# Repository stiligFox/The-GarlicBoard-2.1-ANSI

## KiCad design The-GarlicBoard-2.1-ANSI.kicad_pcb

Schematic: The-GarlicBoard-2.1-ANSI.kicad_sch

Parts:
C1, C2, C4, C6, C7, C8, C9, C10, C11, C15: 100nF; C_0402_1005Metric; Manufacturer Part No CL05B104KO5NNNC; LCSC C1525
C3, C5: 1uF; C_0402_1005Metric; Manufacturer Part No CL05A105KA5NQNC; LCSC C52923
C12, C13: 27pF; C_0402_1005Metric; Manufacturer Part No 0402CG270J500NT; LCSC C1557
C14, C16: 10uF; C_0805_2012Metric; Manufacturer Part No CL05A106MQ5NUNC; LCSC C1713
C17: 22uF; CP_EIA-3216-10_Kemet-I; LCSC C7171
C18, C21: 1uF; C_0603_1608Metric; LCSC C1592
C19, C20, C22: 100nF; C_0402_1005Metric; LCSC C1525
D1, D2, D3, D4, D5, D6, D7, D8, D9, D10, D11, D12, D13, D14, D15, D16, D17, D18, D19, D20, D21, D22, D23, D24, D25, D26, D27, D28, D29, D30, D31, D32, D33, D34, D35, D36, D37, D38, D39, D40, D41, D42, D43, D44, D45, D46, D47, D48, D49, D50, D51, D52, D53, D54, D55, D56, D57, D58, D59, D60, D61, D62, D63, D64, D65: D; D_SOD-523; Manufacturer Part No 1N5819WS; LCSC C282366
H1, H2, H3, H4, H5, H6, H7: MH; MountingHole_2.2mm_M2
J1, J3, J4, J5, J6: PAD_SQUARE_1MM
J2, J7: Molex Pico-EZMATE; Molex_Pico-EZmate_78171-0004_1x04-1MP_P1.20mm_Vertical; Manufacturer Part No 78170004; LCSC C588524
LED1: Debug LED; LED_0603_1608Metric; Manufacturer Part No C2290; LCSC C2290
Q1: Q_PMOS_GSD; SOT-323_SC-70; Manufacturer Part No DMP2165UW-7; LCSC C388477
R1, R2: 27.4; R_0402_1005Metric; Manufacturer Part No 0402WGF274JTCE; LCSC C31439
R3, R25, R26: 1k; R_0402_1005Metric; Manufacturer Part No 0402WGF1001TCE; LCSC C11702
R6: 120; R_0402_1005Metric; Manufacturer Part No 0402WGF1200TCE; LCSC C25079
R7, R10, R13, R16, R19, R22: 33; R_0603_1608Metric; LCSC C23140
R8, R9, R11, R12, R14, R15, R17, R18, R20, R21, R23, R24: 28; R_0603_1608Metric; LCSC C22973
R27: DNF; R_0402_1005Metric
R28: 10k; R_0402_1005Metric; LCSC C25531
RGB1, RGB2, RGB3, RGB4, RGB5, RGB6, RGB7, RGB8, RGB9, RGB10, RGB11, RGB12, RGB13, RGB14, RGB15, RGB16, RGB17, RGB18, RGB19, RGB20, RGB21, RGB22, RGB23, RGB24, RGB25, RGB26, RGB27, RGB28, RGB29, RGB30, RGB31, RGB32, RGB33, RGB34, RGB35, RGB36, RGB37, RGB38, RGB39, RGB40, RGB41, RGB42, RGB43, RGB44, RGB45, RGB46, RGB47, RGB48, RGB49, RGB50, RGB51, RGB52, RGB53, RGB54, RGB55, RGB56, RGB57, RGB58, RGB59, RGB60, RGB61, RGB62, RGB63, RGB64: LED_RGBA; LED_MX_6028R FIXED; LCSC C183826
ST1, ST5: Stabilizer; STAB_MX_3u
ST2, ST3: Stabilizer; STAB_MX_2.25u
ST4: Stabilizer; STAB_MX_2.75u
SW1: ESC; SW_MX_HS_1.5u; Manufacturer Part No CPG151101S11-1; LCSC C5156480
SW2: TAB; SW_MX_HS_1.75u; Manufacturer Part No CPG151101S11-1; LCSC C5156480
SW3: L_SHIFT; SW_MX_HS_1u; Manufacturer Part No CPG151101S11-1; LCSC C5156480
SW4: L_CTRL; SW_MX_HS_1.25u; Manufacturer Part No CPG151101S11-1; LCSC C5156480
SW5: Q; SW_MX_HS_1u; Manufacturer Part No CPG151101S11-1; LCSC C5156480
SW6: A; SW_MX_HS_1u; Manufacturer Part No CPG151101S11-1; LCSC C5156480
SW7: Z; SW_MX_HS_1u; Manufacturer Part No CPG151101S11-1; LCSC C5156480
SW8: L_ALT; SW_MX_HS_1.25u; Manufacturer Part No CPG151101S11-1; LCSC C5156480
SW9: W; SW_MX_HS_1u; Manufacturer Part No CPG151101S11-1; LCSC C5156480
SW10: S; SW_MX_HS_1u; Manufacturer Part No CPG151101S11-1; LCSC C5156480
SW11: X; SW_MX_HS_1u; Manufacturer Part No CPG151101S11-1; LCSC C5156480
SW12: L_CMD; SW_MX_HS_1.25u; Manufacturer Part No CPG151101S11-1; LCSC C5156480
SW13: E; SW_MX_HS_1u; Manufacturer Part No CPG151101S11-1; LCSC C5156480
SW14: D; SW_MX_HS_1u; Manufacturer Part No CPG151101S11-1; LCSC C5156480
SW15: C; SW_MX_HS_1u; Manufacturer Part No CPG151101S11-1; LCSC C5156480
SW16: R; SW_MX_HS_1u; Manufacturer Part No CPG151101S11-1; LCSC C5156480
SW17: F; SW_MX_HS_1u; Manufacturer Part No CPG151101S11-1; LCSC C5156480
SW18: V; SW_MX_HS_1u; Manufacturer Part No CPG151101S11-1; LCSC C5156480
SW19: FN_1; SW_MX_HS_1u; Manufacturer Part No CPG151101S11-1; LCSC C5156480
SW20: T; SW_MX_HS_1u; Manufacturer Part No CPG151101S11-1; LCSC C5156480
SW21: G; SW_MX_HS_1u; Manufacturer Part No CPG151101S11-1; LCSC C5156480
SW22: B; SW_MX_HS_1u; Manufacturer Part No CPG151101S11-1; LCSC C5156480
SW23: Y; SW_MX_HS_1u; Manufacturer Part No CPG151101S11-1; LCSC C5156480
SW24: H; SW_MX_HS_1u; Manufacturer Part No CPG151101S11-1; LCSC C5156480
SW25: N; SW_MX_HS_1u; Manufacturer Part No CPG151101S11-1; LCSC C5156480
SW26: SPACE; SW_MX_HS_1u; Manufacturer Part No CPG151101S11-1; LCSC C5156480
SW27: U; SW_MX_HS_1u; Manufacturer Part No CPG151101S11-1; LCSC C5156480
SW28: J; SW_MX_HS_1u; Manufacturer Part No CPG151101S11-1; LCSC C5156480
SW29: M; SW_MX_HS_1u; Manufacturer Part No CPG151101S11-1; LCSC C5156480
SW30: I; SW_MX_HS_1u; Manufacturer Part No CPG151101S11-1; LCSC C5156480
SW31: K; SW_MX_HS_1u; Manufacturer Part No CPG151101S11-1; LCSC C5156480
SW32: COMMA; SW_MX_HS_1u; Manufacturer Part No CPG151101S11-1; LCSC C5156480
SW33: R_CMD; SW_MX_HS_1.25u; Manufacturer Part No CPG151101S11-1; LCSC C5156480
SW34: O; SW_MX_HS_1u; Manufacturer Part No CPG151101S11-1; LCSC C5156480
SW35: L; SW_MX_HS_1u; Manufacturer Part No CPG151101S11-1; LCSC C5156480
SW36: PERIOD; SW_MX_HS_1u; Manufacturer Part No CPG151101S11-1; LCSC C5156480
SW37: P; SW_MX_HS_1u; Manufacturer Part No CPG151101S11-1; LCSC C5156480
SW38: SEMI_COLON; SW_MX_HS_1u; Manufacturer Part No CPG151101S11-1; LCSC C5156480
SW39: SLASH; SW_MX_HS_1u; Manufacturer Part No CPG151101S11-1; LCSC C5156480
SW40: R_ALT; SW_MX_HS_1.25u; Manufacturer Part No CPG151101S11-1; LCSC C5156480
SW41: HYPHEN; SW_MX_HS_1u; Manufacturer Part No CPG151101S11-1; LCSC C5156480
SW42: APOSTROPHE; SW_MX_HS_1u; Manufacturer Part No CPG151101S11-1; LCSC C5156480
SW43: R_CTRL; SW_MX_HS_1.25u; Manufacturer Part No CPG151101S11-1; LCSC C5156480
SW44: EQUALS; SW_MX_HS_1u; Manufacturer Part No CPG151101S11-1; LCSC C5156480
SW45: RETURN; SW_MX_HS_1u; Manufacturer Part No CPG151101S11-1; LCSC C5156480
SW46: FN_2; SW_MX_HS_1.5u; Manufacturer Part No CPG151101S11-1; LCSC C5156480
SW47: BCK_SPC; SW_MX_HS_1.5u; Manufacturer Part No CPG151101S11-1; LCSC C5156480
SW48: R_SHIFT; SW_MX_HS_1u; Manufacturer Part No CPG151101S11-1; LCSC C5156480
SW49: 7; SW_MX_HS_1u; Manufacturer Part No CPG151101S11-1; LCSC C5156480
SW50: 4; SW_MX_HS_1u; Manufacturer Part No CPG151101S11-1; LCSC C5156480
SW51: 1; SW_MX_HS_1u; Manufacturer Part No CPG151101S11-1; LCSC C5156480
SW52: 00; SW_MX_HS_1u; Manufacturer Part No CPG151101S11-1; LCSC C5156480
SW53: 8; SW_MX_HS_1u; Manufacturer Part No CPG151101S11-1; LCSC C5156480
SW54: 5; SW_MX_HS_1u; Manufacturer Part No CPG151101S11-1; LCSC C5156480
SW55: 2; SW_MX_HS_1u; Manufacturer Part No CPG151101S11-1; LCSC C5156480
SW56: 0; SW_MX_HS_1u; Manufacturer Part No CPG151101S11-1; LCSC C5156480
SW57: 9; SW_MX_HS_1u; Manufacturer Part No CPG151101S11-1; LCSC C5156480
SW58: 6; SW_MX_HS_1u; Manufacturer Part No CPG151101S11-1; LCSC C5156480
SW59: 3; SW_MX_HS_1u; Manufacturer Part No CPG151101S11-1; LCSC C5156480
SW60: NUM_PER; SW_MX_HS_1u; Manufacturer Part No CPG151101S11-1; LCSC C5156480
SW61: MINUS; SW_MX_HS_1u; Manufacturer Part No CPG151101S11-1; LCSC C5156480
SW62: PLUS; SW_MX_HS_1u; Manufacturer Part No CPG151101S11-1; LCSC C5156480
SW63: ENTER; SW_MX_HS_1u; Manufacturer Part No CPG151101S11-1; LCSC C5156480
SW64: PAD_LOCK; SW_MX_HS_1u; Manufacturer Part No CPG151101S11-1; LCSC C5156480
SW65: SW_Push; SW_SPST_SKQG_WithStem; Manufacturer Part No B3U-1000P; LCSC C115351
SW66, SW67: SW_Push; SW_SPST_B3U-1000P; Manufacturer Part No B3U-1000P; LCSC C231329
SW68: RotaryEncoder_Switch; RotaryEncoder_Alps_EC11E-Switch_Vertical_H20mm
U1: RP2040; QFN-56-1EP_7x7mm_P0.4mm_EP3.2x3.2mm; Manufacturer Part No RP2040; LCSC C2040
U2: W25Q128JVS; SOIC-8_5.23x5.23mm_P1.27mm; Manufacturer Part No W25Q128JVSIQ; LCSC C97521
U3: NCP1117-3.3_SOT223; SOT-223-3_TabPin2; Manufacturer Part No NCP1117ST33T3G; LCSC C26537
U4: AW20216SQNR; QFN-44_EP_5x5_Pitch0.4mm; Manufacturer Part AW20216SQNR; LCSC Part Name AW20216SQNR
Y1: 12MHz; Crystal_SMD_3225-4Pin_3.2x2.5mm; Manufacturer Part No X322512MSB4SI; LCSC C9002

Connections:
+1V1: C1.1, C2.1, C3.1, U1.23 (DVDD), U1.45 (VREG_VOUT), U1.50 (DVDD)
+3V3: C4.1, C5.1, C6.1, C7.1, C8.1, C9.1, C10.1, C11.1, C15.1, C16.1, J3.1, R3.2, R27.2, U1.1 (IOVDD), U1.10 (IOVDD), U1.22 (IOVDD), U1.33 (IOVDD), U1.42 (IOVDD), U1.43 (ADC_AVDD), U1.44 (VREG_IN), U1.48 (USB_VDD), U1.49 (IOVDD), U2.8 (VCC), U3.2 (VO)
+5V: C14.1, C17.1, C18.1, C19.1, C20.1, C21.1, C22.1, J2.2, Q1.2 (S), U3.3 (VI), U4.6 (PVCC), U4.24 (VCC), U4.29 (EN)
/~USB_BOOT: R26.1, SW65.2, SW66.2
COL0: SW1.2, SW2.2, SW3.2, SW4.2, SW5.2, SW6.2, SW7.2, SW8.2, U1.34 (GPIO22)
COL1: SW9.2, SW10.2, SW11.2, SW12.2, SW13.2, SW14.2, SW15.2, U1.32 (GPIO21)
COL2: SW16.2, SW17.2, SW18.2, SW19.2, SW20.2, SW21.2, SW22.2, U1.31 (GPIO20)
COL3: SW23.2, SW24.2, SW25.2, SW26.2, SW27.2, SW28.2, SW29.2, U1.30 (GPIO19)
COL4: SW30.2, SW31.2, SW32.2, SW33.2, SW34.2, SW35.2, SW36.2, U1.29 (GPIO18)
COL5: SW37.2, SW38.2, SW39.2, SW40.2, SW41.2, SW42.2, SW43.2, U1.28 (GPIO17)
COL6: SW44.2, SW45.2, SW46.2, SW47.2, SW48.2, SW68.S2, U1.27 (GPIO16)
COL7: SW49.2, SW50.2, SW51.2, SW52.2, SW53.2, SW54.2, SW55.2, SW56.2, U1.7 (GPIO5)
COL8: SW57.2, SW58.2, SW59.2, SW60.2, SW61.2, SW62.2, SW63.2, SW64.2, U1.6 (GPIO4)
CS1: R24.2, U4.43 (CS1)
CS2: R23.2, U4.42 (CS2)
CS3: R22.2, U4.41 (CS3)
CS4: R21.2, U4.40 (CS4)
CS5: R20.2, U4.38 (CS5)
CS6: R19.2, U4.37 (CS6)
CS7: R18.2, U4.36 (CS7)
CS8: R17.2, U4.35 (CS8)
CS9: R16.2, U4.34 (CS9)
CS10: R15.2, U4.22 (CS10)
CS11: R14.2, U4.21 (CS11)
CS12: R13.2, U4.20 (CS12)
CS13: R12.2, U4.19 (CS13)
CS14: R11.2, U4.18 (CS14)
CS15: R10.2, U4.16 (CS15)
CS16: R9.2, U4.15 (CS16)
CS17: R8.2, U4.14 (CS17)
CS18: R7.2, U4.13 (CS18)
DN: J7.2, R2.1
DP: J7.3, R1.1
ENCSW1: D48.2 (A), SW68.S1
ENC_A: SW68.A, U1.40 (GPIO28_ADC2)
ENC_B: SW68.B, U1.41 (GPIO29_ADC3)
GND: C1.2, C2.2, C3.2, C4.2, C5.2, C6.2, C7.2, C8.2, C9.2, C10.2, C11.2, C12.1, C13.1, C14.2, C15.2, C16.2, C17.2, C18.2, C19.2, C20.2, C21.2, C22.2, J2.1, J2.MP (MountPin), J6.1, J7.4, J7.MP (MountPin), LED1.1 (K), Q1.1 (G), R28.2, SW65.1, SW66.1, SW67.1, SW68.C, SW68.MP (MountPin), U1.19 (TESTEN), U1.57 (GND), U2.4 (GND), U3.1 (GND), U4.17 (PGND), U4.26 (GND), U4.39 (PGND), U4.45 (GND), Y1.2, Y1.4
unnamed: C13.2, R25.1, Y1.1
unnamed: D1.2 (A), SW1.1
unnamed: D2.2 (A), SW2.1
unnamed: D3.2 (A), SW3.1
unnamed: D4.2 (A), SW4.1
unnamed: D5.2 (A), SW5.1
unnamed: D6.2 (A), SW6.1
unnamed: D7.2 (A), SW7.1
unnamed: D8.2 (A), SW8.1
unnamed: D9.2 (A), SW9.1
unnamed: D10.2 (A), SW10.1
unnamed: D11.2 (A), SW11.1
unnamed: D12.2 (A), SW12.1
unnamed: D13.2 (A), SW13.1
unnamed: D14.2 (A), SW14.1
unnamed: D15.2 (A), SW15.1
unnamed: D16.2 (A), SW16.1
unnamed: D17.2 (A), SW17.1
unnamed: D18.2 (A), SW18.1
unnamed: D19.2 (A), SW19.1
unnamed: D20.2 (A), SW20.1
unnamed: D21.2 (A), SW21.1
unnamed: D22.2 (A), SW22.1
unnamed: D23.2 (A), SW23.1
unnamed: D24.2 (A), SW24.1
unnamed: D25.2 (A), SW25.1
unnamed: D26.2 (A), SW26.1
unnamed: D27.2 (A), SW27.1
unnamed: D28.2 (A), SW28.1
unnamed: D29.2 (A), SW29.1
unnamed: D30.2 (A), SW30.1
unnamed: D31.2 (A), SW31.1
unnamed: D32.2 (A), SW32.1
unnamed: D33.2 (A), SW33.1
unnamed: D34.2 (A), SW34.1
unnamed: D35.2 (A), SW35.1
unnamed: D36.2 (A), SW36.1
unnamed: D37.2 (A), SW37.1
unnamed: D38.2 (A), SW38.1
unnamed: D39.2 (A), SW39.1
unnamed: D40.2 (A), SW40.1
unnamed: D41.2 (A), SW41.1
unnamed: D42.2 (A), SW42.1
unnamed: D43.2 (A), SW43.1
unnamed: D44.2 (A), SW44.1
unnamed: D45.2 (A), SW45.1
unnamed: D46.2 (A), SW46.1
unnamed: D47.2 (A), SW47.1
unnamed: D49.2 (A), SW48.1
unnamed: D50.2 (A), SW49.1
unnamed: D51.2 (A), SW50.1
unnamed: D52.2 (A), SW51.1
unnamed: D53.2 (A), SW52.1
unnamed: D54.2 (A), SW53.1
unnamed: D55.2 (A), SW54.1
unnamed: D56.2 (A), SW55.1
unnamed: D57.2 (A), SW56.1
unnamed: D58.2 (A), SW57.1
unnamed: D59.2 (A), SW58.1
unnamed: D60.2 (A), SW59.1
unnamed: D61.2 (A), SW60.1
unnamed: D62.2 (A), SW61.1
unnamed: D63.2 (A), SW62.1
unnamed: D64.2 (A), SW63.1
unnamed: D65.2 (A), SW64.1
unnamed: J7.1, Q1.3 (D)
unnamed: LED1.2 (A), R6.2
unnamed: R9.1, RGB1.3 (BK), RGB2.3 (BK), RGB3.3 (BK), RGB4.3 (BK), RGB5.3 (BK), RGB6.3 (BK), RGB7.3 (BK), RGB8.3 (BK), RGB9.3 (BK), RGB10.3 (BK), RGB11.3 (BK), RGB12.3 (BK)
unnamed: R8.1, RGB1.2 (GK), RGB2.2 (GK), RGB3.2 (GK), RGB4.2 (GK), RGB5.2 (GK), RGB6.2 (GK), RGB7.2 (GK), RGB8.2 (GK), RGB9.2 (GK), RGB10.2 (GK), RGB11.2 (GK), RGB12.2 (GK)
unnamed: R7.1, RGB1.1 (RK), RGB2.1 (RK), RGB3.1 (RK), RGB4.1 (RK), RGB5.1 (RK), RGB6.1 (RK), RGB7.1 (RK), RGB8.1 (RK), RGB9.1 (RK), RGB10.1 (RK), RGB11.1 (RK), RGB12.1 (RK)
unnamed: R12.1, RGB13.3 (BK), RGB14.3 (BK), RGB15.3 (BK), RGB16.3 (BK), RGB17.3 (BK), RGB18.3 (BK), RGB19.3 (BK), RGB20.3 (BK), RGB21.3 (BK), RGB22.3 (BK)
unnamed: R11.1, RGB13.2 (GK), RGB14.2 (GK), RGB15.2 (GK), RGB16.2 (GK), RGB17.2 (GK), RGB18.2 (GK), RGB19.2 (GK), RGB20.2 (GK), RGB21.2 (GK), RGB22.2 (GK)
unnamed: R10.1, RGB13.1 (RK), RGB14.1 (RK), RGB15.1 (RK), RGB16.1 (RK), RGB17.1 (RK), RGB18.1 (RK), RGB19.1 (RK), RGB20.1 (RK), RGB21.1 (RK), RGB22.1 (RK)
unnamed: R15.1, RGB23.3 (BK), RGB24.3 (BK), RGB25.3 (BK), RGB26.3 (BK), RGB27.3 (BK), RGB28.3 (BK), RGB29.3 (BK), RGB30.3 (BK), RGB31.3 (BK), RGB32.3 (BK)
unnamed: R14.1, RGB23.2 (GK), RGB24.2 (GK), RGB25.2 (GK), RGB26.2 (GK), RGB27.2 (GK), RGB28.2 (GK), RGB29.2 (GK), RGB30.2 (GK), RGB31.2 (GK), RGB32.2 (GK)
unnamed: R13.1, RGB23.1 (RK), RGB24.1 (RK), RGB25.1 (RK), RGB26.1 (RK), RGB27.1 (RK), RGB28.1 (RK), RGB29.1 (RK), RGB30.1 (RK), RGB31.1 (RK), RGB32.1 (RK)
unnamed: R18.1, RGB33.3 (BK), RGB34.3 (BK), RGB35.3 (BK), RGB36.3 (BK), RGB37.3 (BK), RGB38.3 (BK), RGB39.3 (BK), RGB40.3 (BK), RGB41.3 (BK), RGB42.3 (BK)
unnamed: R17.1, RGB33.2 (GK), RGB34.2 (GK), RGB35.2 (GK), RGB36.2 (GK), RGB37.2 (GK), RGB38.2 (GK), RGB39.2 (GK), RGB40.2 (GK), RGB41.2 (GK), RGB42.2 (GK)
unnamed: R16.1, RGB33.1 (RK), RGB34.1 (RK), RGB35.1 (RK), RGB36.1 (RK), RGB37.1 (RK), RGB38.1 (RK), RGB39.1 (RK), RGB40.1 (RK), RGB41.1 (RK), RGB42.1 (RK)
unnamed: R21.1, RGB43.3 (BK), RGB44.3 (BK), RGB45.3 (BK), RGB46.3 (BK), RGB47.3 (BK), RGB48.3 (BK), RGB49.3 (BK), RGB50.3 (BK), RGB51.3 (BK), RGB52.3 (BK)
unnamed: R20.1, RGB43.2 (GK), RGB44.2 (GK), RGB45.2 (GK), RGB46.2 (GK), RGB47.2 (GK), RGB48.2 (GK), RGB49.2 (GK), RGB50.2 (GK), RGB51.2 (GK), RGB52.2 (GK)
unnamed: R19.1, RGB43.1 (RK), RGB44.1 (RK), RGB45.1 (RK), RGB46.1 (RK), RGB47.1 (RK), RGB48.1 (RK), RGB49.1 (RK), RGB50.1 (RK), RGB51.1 (RK), RGB52.1 (RK)
unnamed: R24.1, RGB53.3 (BK), RGB54.3 (BK), RGB55.3 (BK), RGB56.3 (BK), RGB57.3 (BK), RGB58.3 (BK), RGB59.3 (BK), RGB60.3 (BK), RGB61.3 (BK), RGB62.3 (BK), RGB63.3 (BK), RGB64.3 (BK)
unnamed: R23.1, RGB53.2 (GK), RGB54.2 (GK), RGB55.2 (GK), RGB56.2 (GK), RGB57.2 (GK), RGB58.2 (GK), RGB59.2 (GK), RGB60.2 (GK), RGB61.2 (GK), RGB62.2 (GK), RGB63.2 (GK), RGB64.2 (GK)
unnamed: R22.1, RGB53.1 (RK), RGB54.1 (RK), RGB55.1 (RK), RGB56.1 (RK), RGB57.1 (RK), RGB58.1 (RK), RGB59.1 (RK), RGB60.1 (RK), RGB61.1 (RK), RGB62.1 (RK), RGB63.1 (RK), RGB64.1 (RK)
unnamed: R6.1, U1.15 (GPIO12)
unnamed: J1.1, U1.35 (GPIO23)
unnamed: R2.2, U1.46 (USB_DM)
unnamed: R1.2, U1.47 (USB_DP)
unnamed: R28.1, U4.32 (ISET)
QSPI_SCLK: U1.52 (QSPI_SCLK), U2.6 (CLK)
QSPI_SD0: U1.53 (QSPI_SD0), U2.5 (DI(IO0))
QSPI_SD1: U1.55 (QSPI_SD1), U2.2 (DO(IO1))
QSPI_SD2: U1.54 (QSPI_SD2), U2.3 (IO2)
QSPI_SD3: U1.51 (QSPI_SD3), U2.7 (IO3)
QSPI_SS: R26.2, R27.1, U1.56 (QSPI_SS), U2.1 (~CS)
RESET: R3.1, SW67.2, U1.26 (RUN)
ROW0: D1.1 (K), D9.1 (K), D16.1 (K), D23.1 (K), D30.1 (K), D37.1 (K), D44.1 (K), D50.1 (K), D58.1 (K), U1.2 (GPIO0)
ROW1: D2.1 (K), D10.1 (K), D17.1 (K), D24.1 (K), D31.1 (K), D38.1 (K), D45.1 (K), D51.1 (K), D59.1 (K), U1.4 (GPIO2)
ROW2: D3.1 (K), D11.1 (K), D18.1 (K), D25.1 (K), D32.1 (K), D39.1 (K), D52.1 (K), D60.1 (K), U1.8 (GPIO6)
ROW3: D4.1 (K), D12.1 (K), D19.1 (K), D26.1 (K), D33.1 (K), D40.1 (K), D46.1 (K), D53.1 (K), D61.1 (K), U1.13 (GPIO10)
ROW4: D5.1 (K), D13.1 (K), D20.1 (K), D27.1 (K), D34.1 (K), D41.1 (K), D47.1 (K), D54.1 (K), D62.1 (K), U1.3 (GPIO1)
ROW5: D6.1 (K), D14.1 (K), D21.1 (K), D28.1 (K), D35.1 (K), D42.1 (K), D48.1 (K), D55.1 (K), D63.1 (K), U1.5 (GPIO3)
ROW6: D7.1 (K), D15.1 (K), D22.1 (K), D29.1 (K), D36.1 (K), D49.1 (K), D56.1 (K), D64.1 (K), U1.9 (GPIO7)
ROW7: D8.1 (K), D43.1 (K), D57.1 (K), D65.1 (K), U1.14 (GPIO11)
SCL: J2.3, U1.18 (GPIO15)
SDA: J2.4, U1.17 (GPIO14)
SPI1 CSn: U1.37 (GPIO25), U4.28 (CSN)
SPI1 RX: U1.36 (GPIO24), U4.27 (MISO)
SPI1 SCK: U1.38 (GPIO26_ADC0), U4.31 (SCK)
SPI1 TX: U1.39 (GPIO27_ADC1), U4.30 (MOSI)
SW1: RGB12.4 (A), RGB52.4 (A), RGB64.4 (A), U4.7 (SW1)
SW2: RGB11.4 (A), RGB22.4 (A), RGB32.4 (A), RGB51.4 (A), RGB63.4 (A), U4.5 (SW2)
SW3: RGB10.4 (A), RGB21.4 (A), RGB31.4 (A), RGB42.4 (A), RGB50.4 (A), RGB62.4 (A), U4.8 (SW3)
SW4: RGB9.4 (A), RGB20.4 (A), RGB30.4 (A), RGB41.4 (A), RGB49.4 (A), RGB61.4 (A), U4.4 (SW4)
SW5: RGB8.4 (A), RGB19.4 (A), RGB29.4 (A), RGB40.4 (A), RGB48.4 (A), RGB60.4 (A), U4.9 (SW5)
SW6: RGB7.4 (A), RGB18.4 (A), RGB28.4 (A), RGB39.4 (A), RGB47.4 (A), RGB59.4 (A), U4.3 (SW6)
SW7: RGB6.4 (A), RGB17.4 (A), RGB27.4 (A), RGB38.4 (A), RGB46.4 (A), RGB58.4 (A), U4.10 (SW7)
SW8: RGB5.4 (A), RGB37.4 (A), RGB45.4 (A), RGB57.4 (A), U4.2 (SW8)
SW9: RGB4.4 (A), RGB16.4 (A), RGB26.4 (A), RGB36.4 (A), RGB44.4 (A), RGB56.4 (A), U4.11 (SW9)
SW10: RGB3.4 (A), RGB15.4 (A), RGB25.4 (A), RGB35.4 (A), RGB55.4 (A), U4.1 (SW10)
SW11: RGB2.4 (A), RGB14.4 (A), RGB24.4 (A), RGB34.4 (A), RGB54.4 (A), U4.12 (SW11)
SW12: RGB1.4 (A), RGB13.4 (A), RGB23.4 (A), RGB33.4 (A), RGB43.4 (A), RGB53.4 (A), U4.44 (SW12)
SWCLK: J5.1, U1.24 (SWCLK)
SWDIO: J4.1, U1.25 (SWD)
XIN: C12.2, U1.20 (XIN), Y1.3
XOUT: R25.2, U1.21 (XOUT)

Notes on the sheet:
STORAGE
KEYBOARD INTERFACE
OLED
v2.0_230104
LED CONTROLLER
MCU
CLOCK
ROTARY ENCODER
MOUNTING HOLES
The GarlicBoard
RESET
UDB CONNECTOR
The GarlicBoard stiligFox
SWITCH MATRIX
CONNECTOR TO UNIFIED DAUGHTERBOARD VOLTAGE REGULATOR
May 1, 2022 - July 12, 2025

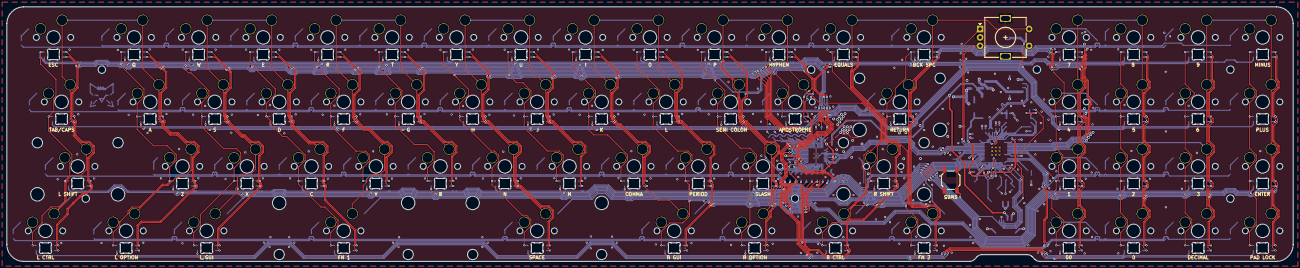
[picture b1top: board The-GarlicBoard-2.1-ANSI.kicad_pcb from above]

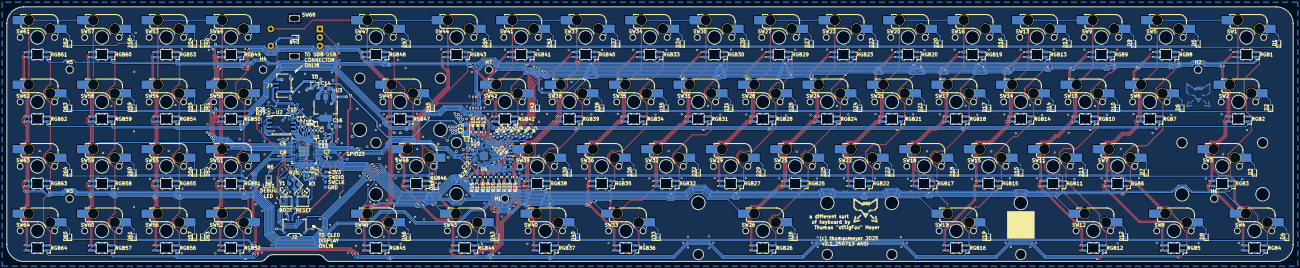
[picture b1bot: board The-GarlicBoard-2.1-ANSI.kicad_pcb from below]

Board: 2 copper layers, 379.9 x 75.1 mm, 271 parts (258 on the bottom side), 164 nets.

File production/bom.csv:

Designator,Footprint,Quantity,Value,LCSC Part #
"C1, C10, C11, C15, C19, C2, C20, C22, C4, C6, C7, C8, C9",0402,13,100nF,C1525
"C12, C13",0402,2,27pF,C1557
"C14, C16",0805,2,10uF,C1713
C17,CP_EIA-3216-10_Kemet-I,1,22uF,C7171
"C18, C21",0603,2,1uF,C1592
"C3, C5",0402,2,1uF,C52923
"D1, D10, D11, D12, D13, D14, D15, D16, D17, D18, D19, D2, D20, D21, D22, D23, D24, D25, D26, D27, D28, D29, D3, D30, D31, D32, D33, D34, D35, D36, D37, D38, D39, D4, D40, D41, D42, D43, D44, D45, D46, D47, D48, D49, D5, D50, D51, D52, D53, D54, D55, D56, D57, D58, D59, D6, D60, D61, D62, D63, D64, D65, D7, D8, D9",D_SOD-523,65,D,C282366
"H1, H2, H3, H4, H5, H6, H7",MountingHole_2.2mm_M2,7,MH,
"J1, J3, J4, J5, J6",PAD_SQUARE_1MM,5,PAD_SQUARE_1MM,
"J2, J7",Molex_Pico-EZmate_78171-0004_1x04-1MP_P1.20mm_Vertical,2,Molex Pico-EZMATE,C588524
LED1,0603,1,Debug LED,C2290
Q1,SOT-323_SC-70,1,Q_PMOS_GSD,C388477
"R1, R2",0402,2,27.4,C31439
"R10, R13, R16, R19, R22, R7",0603,6,33,C23140
"R11, R12, R14, R15, R17, R18, R20, R21, R23, R24, R8, R9",0603,12,28,C22973
"R25, R26, R3",0402,3,1k,C11702
R27,0402,1,DNF,
R28,0402,1,10k,C25531
R6,0402,1,120,C25079
"RGB1, RGB10, RGB11, RGB12, RGB13, RGB14, RGB15, RGB16, RGB17, RGB18, RGB19, RGB2, RGB20, RGB21, RGB22, RGB23, RGB24, RGB25, RGB26, RGB27, RGB28, RGB29, RGB3, RGB30, RGB31, RGB32, RGB33, RGB34, RGB35, RGB36, RGB37, RGB38, RGB39, RGB4, RGB40, RGB41, RGB42, RGB43, RGB44, RGB45, RGB46, RGB47, RGB48, RGB49, RGB5, RGB50, RGB51, RGB52, RGB53, RGB54, RGB55, RGB56, RGB57, RGB58, RGB59, RGB6, RGB60, RGB61, RGB62, RGB63, RGB64, RGB7, RGB8, RGB9",LED_MX_6028R FIXED,64,LED_RGBA,C183826
SW1,SW_MX_HS_1.5u,1,ESC,C5156480
SW10,SW_MX_HS_1u,1,S,C5156480
SW11,SW_MX_HS_1u,1,X,C5156480
SW12,SW_MX_HS_1.25u,1,L_CMD,C5156480
SW13,SW_MX_HS_1u,1,E,C5156480
SW14,SW_MX_HS_1u,1,D,C5156480
SW15,SW_MX_HS_1u,1,C,C5156480
SW16,SW_MX_HS_1u,1,R,C5156480
SW17,SW_MX_HS_1u,1,F,C5156480
SW18,SW_MX_HS_1u,1,V,C5156480
SW19,SW_MX_HS_1u,1,FN_1,C5156480
SW2,SW_MX_HS_1.75u,1,TAB,C5156480
SW20,SW_MX_HS_1u,1,T,C5156480
SW21,SW_MX_HS_1u,1,G,C5156480
SW22,SW_MX_HS_1u,1,B,C5156480
SW23,SW_MX_HS_1u,1,Y,C5156480
SW24,SW_MX_HS_1u,1,H,C5156480
SW25,SW_MX_HS_1u,1,N,C5156480
SW26,SW_MX_HS_1u,1,SPACE,C5156480
SW27,SW_MX_HS_1u,1,U,C5156480
SW28,SW_MX_HS_1u,1,J,C5156480
SW29,SW_MX_HS_1u,1,M,C5156480
SW3,SW_MX_HS_1u,1,L_SHIFT,C5156480
SW30,SW_MX_HS_1u,1,I,C5156480
SW31,SW_MX_HS_1u,1,K,C5156480
SW32,SW_MX_HS_1u,1,COMMA,C5156480
SW33,SW_MX_HS_1.25u,1,R_CMD,C5156480
SW34,SW_MX_HS_1u,1,O,C5156480
SW35,SW_MX_HS_1u,1,L,C5156480
SW36,SW_MX_HS_1u,1,PERIOD,C5156480
SW37,SW_MX_HS_1u,1,P,C5156480
SW38,SW_MX_HS_1u,1,SEMI_COLON,C5156480
SW39,SW_MX_HS_1u,1,SLASH,C5156480
SW4,SW_MX_HS_1.25u,1,L_CTRL,C5156480
SW40,SW_MX_HS_1.25u,1,R_ALT,C5156480
SW41,SW_MX_HS_1u,1,HYPHEN,C5156480
SW42,SW_MX_HS_1u,1,APOSTROPHE,C5156480
SW43,SW_MX_HS_1.25u,1,R_CTRL,C5156480
SW44,SW_MX_HS_1u,1,EQUALS,C5156480
SW45,SW_MX_HS_1u,1,RETURN,C5156480
SW46,SW_MX_HS_1.5u,1,FN_2,C5156480
SW47,SW_MX_HS_1.5u,1,BCK_SPC,C5156480
SW48,SW_MX_HS_1u,1,R_SHIFT,C5156480
SW49,SW_MX_HS_1u,1,7,C5156480
SW5,SW_MX_HS_1u,1,Q,C5156480
SW50,SW_MX_HS_1u,1,4,C5156480
SW51,SW_MX_HS_1u,1,1,C5156480
SW52,SW_MX_HS_1u,1,00,C5156480
SW53,SW_MX_HS_1u,1,8,C5156480
SW54,SW_MX_HS_1u,1,5,C5156480
SW55,SW_MX_HS_1u,1,2,C5156480
SW56,SW_MX_HS_1u,1,0,C5156480
SW57,SW_MX_HS_1u,1,9,C5156480
SW58,SW_MX_HS_1u,1,6,C5156480
SW59,SW_MX_HS_1u,1,3,C5156480
SW6,SW_MX_HS_1u,1,A,C5156480
SW60,SW_MX_HS_1u,1,NUM_PER,C5156480
SW61,SW_MX_HS_1u,1,MINUS,C5156480
SW62,SW_MX_HS_1u,1,PLUS,C5156480
SW63,SW_MX_HS_1u,1,ENTER,C5156480
SW64,SW_MX_HS_1u,1,PAD_LOCK,C5156480
SW65,SW_SPST_SKQG_WithStem,1,SW_Push,C115351
SW7,SW_MX_HS_1u,1,Z,C5156480
SW8,SW_MX_HS_1.25u,1,L_ALT,C5156480
SW9,SW_MX_HS_1u,1,W,C5156480
U1,QFN-56-1EP_7x7mm_P0.4mm_EP3.2x3.2mm,1,RP2040,C2040
U2,SOIC-8_5.23x5.23mm_P1.27mm,1,W25Q128JVS,C97521
U3,SOT-223-3_TabPin2,1,NCP1117-3.3_SOT223,C26537
U4,QFN-44_EP_5x5_Pitch0.4mm,1,AW20216SQNR,C7385556
Y1,Crystal_SMD_3225-4Pin_3.2x2.5mm,1,12MHz,C9002

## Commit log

2025-07-04 Initial Commit
    Initial Commit
2025-07-04 No Change
2025-07-05 EdgeCut Updated
2025-07-05 Final Pre-BOM changes
2025-07-06 Parts update
2025-07-12 Final Update
2025-07-16 MAJOR REVISION
    Completely remapped RGB LED matrix - previous version was completely wrong for the LEDs used!
2025-07-17 Minor Updates
2026-06-17 Most recent updates
